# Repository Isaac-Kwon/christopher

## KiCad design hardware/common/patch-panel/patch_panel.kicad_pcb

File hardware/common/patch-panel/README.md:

# Menu patch panel board (common part)

Generated KiCad 10 schematic and **placement-only** PCB of the small board behind the operator panel that carries what the menu
plugging needs besides the letter jacks. Design basis: `hardware/common/design-brief.md` 4.3 (patch panel), 4.5 (test register, test voltage),
`hardware/common/diagonal-board.md` section 4 (what is *not* on the diagonal boards), `hardware/common/test-register/README.md` (J1 cable, J5 TEST lead),
`docs/decisions/0003-interfaces.md` 5.1, 5.2, 7. Build product of the scripts, do not edit by hand.

## Decision: letter jacks stay on the diagonal boards

The design brief puts the letter jacks on the diagonal-board backplane (4.4: "glyph jacks on a backplane PCB with fixed wiring"), and
`diagonal-board.md` section 4 says commons, register-cable jack and searching jack are *not* part of the diagonal nets and go on a separate small
board. So the patch panel is **not folded** into the diagonal boards; it is this separate board (339.5 x 160 mm, one board).

## Content

| Part | Count | Function |
|---|---:|---|
| `CM11..CM44` commons | 4 groups x 4 male D-sub 37 | the four jacks of a group are in parallel (26 lines): one letter can feed more than two scramblers |
| `JR1` / `JR2` register jack | 2 male D-sub 37 | `JR1` front (operator), `JR2` rear (cable to the test register J1), parallel; a cable between the test letter's jack and `JR1` brings that letter's 26 wires to the register |
| `JS1` searching jack + `TS1` hole field | 1 jack + 26 holes (2 x 13 pin socket) | a cable from the test letter's second jack to `JS1`; line k appears at hole k (silk A..Z) |
| `J_TEST` | 2-pole 5.08 terminal | 1 = `TEST` (register J5, +24 V during STROBE), 2 = 0 V |
| `PL1` test plug | flying lead (in the schematic, `on_board = no`) | the end of the TEST lead, pushed into ONE hole of `TS1` = the wire that gets the test voltage (the menu's input wire) |
| `J0V` | 2-pole 5.08 terminal (both pins one net) | the 0 V reference: ONE connection to the 0 V of the power supply (and to `J0V` on diagonal board D1) |
| `R1`, `C1`, 6 plated M3 holes | | `CHASSIS` (shells, holes) to 0 V by 1 Mohm || 10 nF (decision 0003 7.1) |

All jacks are **male** (decision 0003 5.1: boards and panel pins, cables female at both ends, 1:1), pins 1-26 = wire A..Z, **pins 27-29 tied to 0 V here**
(common side; the scrambler-side boards never tie them), 30-37 not connected, shell pads = `CHASSIS`. Layout: 85 x 30 mm grid, rows 1-4 = commons 1-4,
row 5 = `JR1`, `JR2`, `JS1` and the fourth slot with `TS1` (horizontal, hole letters on the silk), `J_TEST`, `J0V`. 4 layers (26-line commons).

## Files

| File | Purpose |
|---|---|
| `ki_common.py` | shared library (identical copy in the other two folders) |
| `gen_patch.py` | -> `patch_panel.kicad_pro/.kicad_sch` |
| `gen_patch_pcb.py` | placement -> `patch_panel.kicad_pcb` |
| `verify_patch.py` | ERC + netlist connectivity + test-plug simulation + negative tests |
| `verify_patch_pcb.py` | board vs schematic, DRC, geometry (pcbnew), negative test |

    python gen_patch.py && python gen_patch_pcb.py && python verify_patch.py && python verify_patch_pcb.py

Build output in `%LOCALAPPDATA%/christopher/patch-panel`.

## Results (KiCad 10.0.4)

| Item | Result |
|---|---|
| ERC (all severities) | 0 violations |
| Parts | 30 (19 jacks, `TS1`, `J_TEST`, `J0V`, `R1`, `C1`, 6 holes) + the flying plug `PL1` |
| Connectivity | each common wire = exactly the 4 jack pins of its group; `JR1`/`JR2` pin k on one net; `JS1` pin k = hole k only; 0 V net = pins 27-29 of all 19 jacks + `J_TEST` 2 + `J0V` + RC, no signal on it; CHASSIS separate from 0 V |
| Test-plug simulation | plug out: `TEST` isolated; plug in hole k (k = 1..26): `TEST` reaches exactly `JS1` pin k and hole k, nothing else |
| Negative tests | swapped wires on a common jack / on `JS1` / in the hole field, `TEST` <-> 0 V swapped on `J_TEST`, wire <-> 0 V pin on `JR2`: all detected |
| Placement DRC | **0 violations**; unconnected = ratsnest 470 (pcbnew count = sum(pads-1)); pad nets = schematic; grid and hole-field order checked from the board; negative test detected |

## Open questions

1. Who connects the register: the permanent register cable (J1) could also go straight to a letter jack; `JR1`/`JR2` are provided because the brief lists a register-cable jack on the panel.
   If the permanent cable is preferred, `JR2`/`JR1` can be dropped.
2. The test plug is a one-pin flying lead into a 2.54 pin-socket field. A sturdier banana/4 mm field and a plug with shrouded 24 V contact (touch protection, 24 V is extra-low voltage)
   are a panel-design choice; contact wear counts like the letter jacks.
3. Whether TEST should also be offered on a third letter (the British machine had a test plug per bank) is outside this design.
4. Board position and size (339.5 x 160) follow the commons grid (layout.md 3.10 "4 x 4 below the drive"); the real cut-out drawing is a mechanical task.
5. Routing is not done (user rule): 16 x 26 common nets (4 pads each), 26 register nets, 26 search nets.

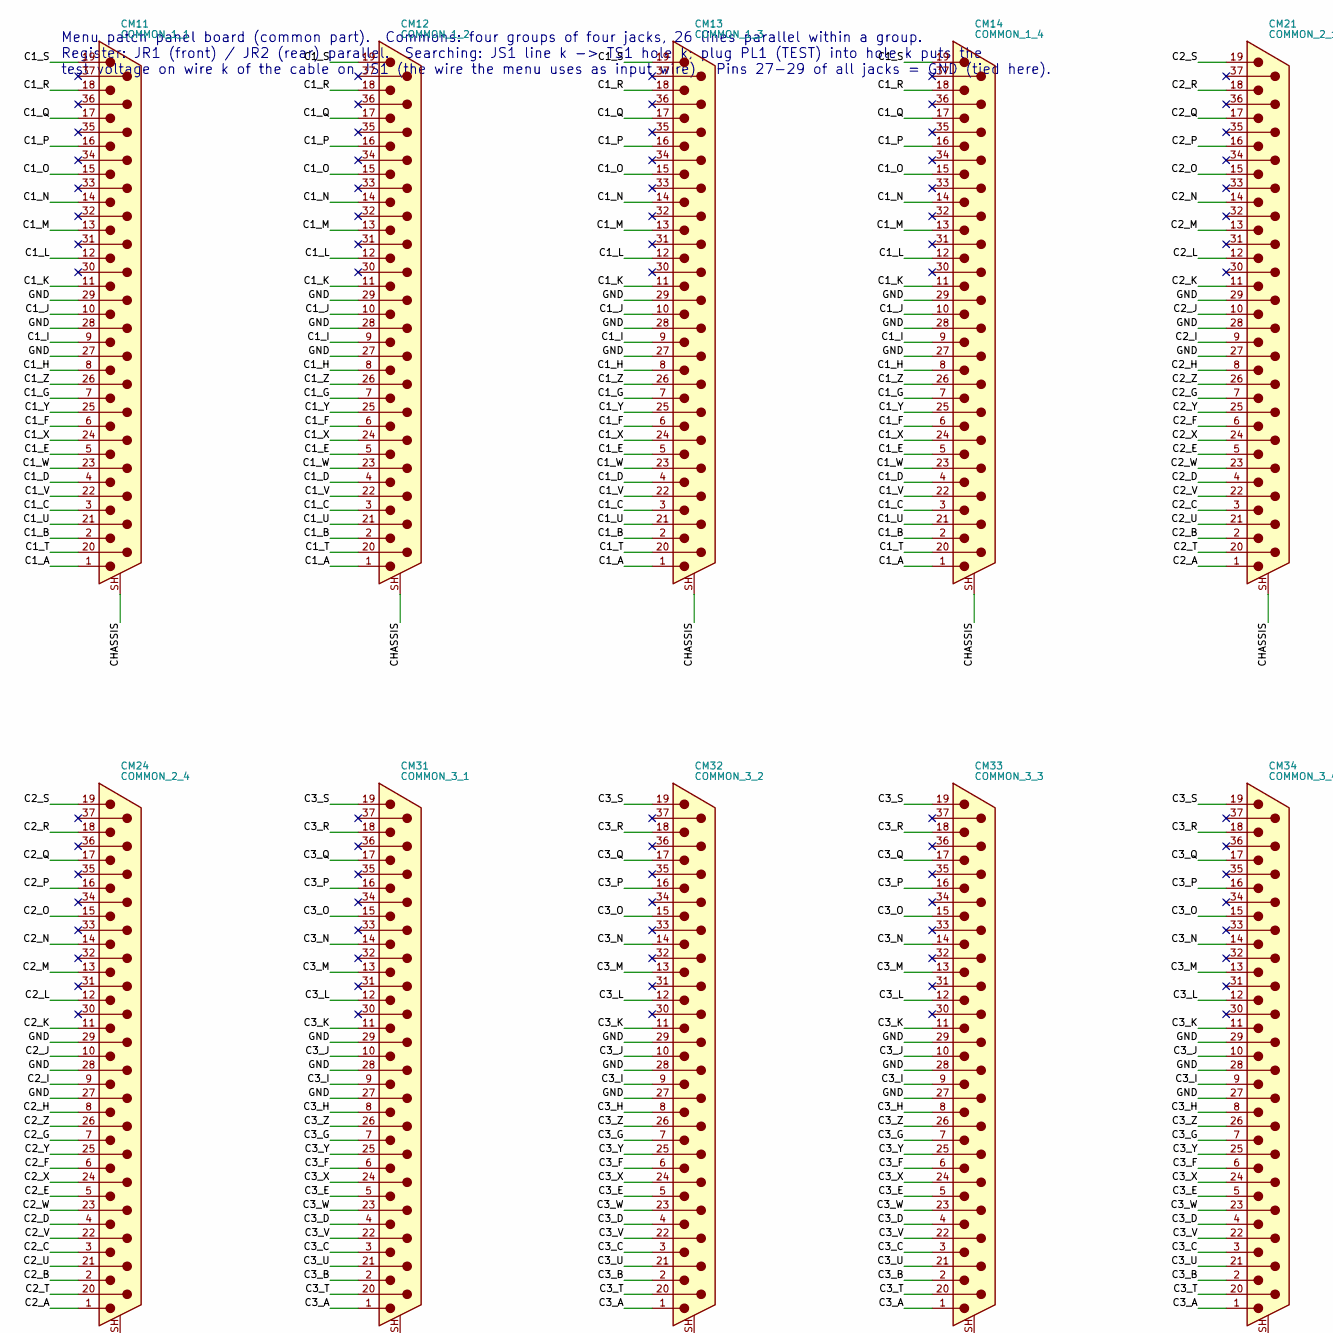
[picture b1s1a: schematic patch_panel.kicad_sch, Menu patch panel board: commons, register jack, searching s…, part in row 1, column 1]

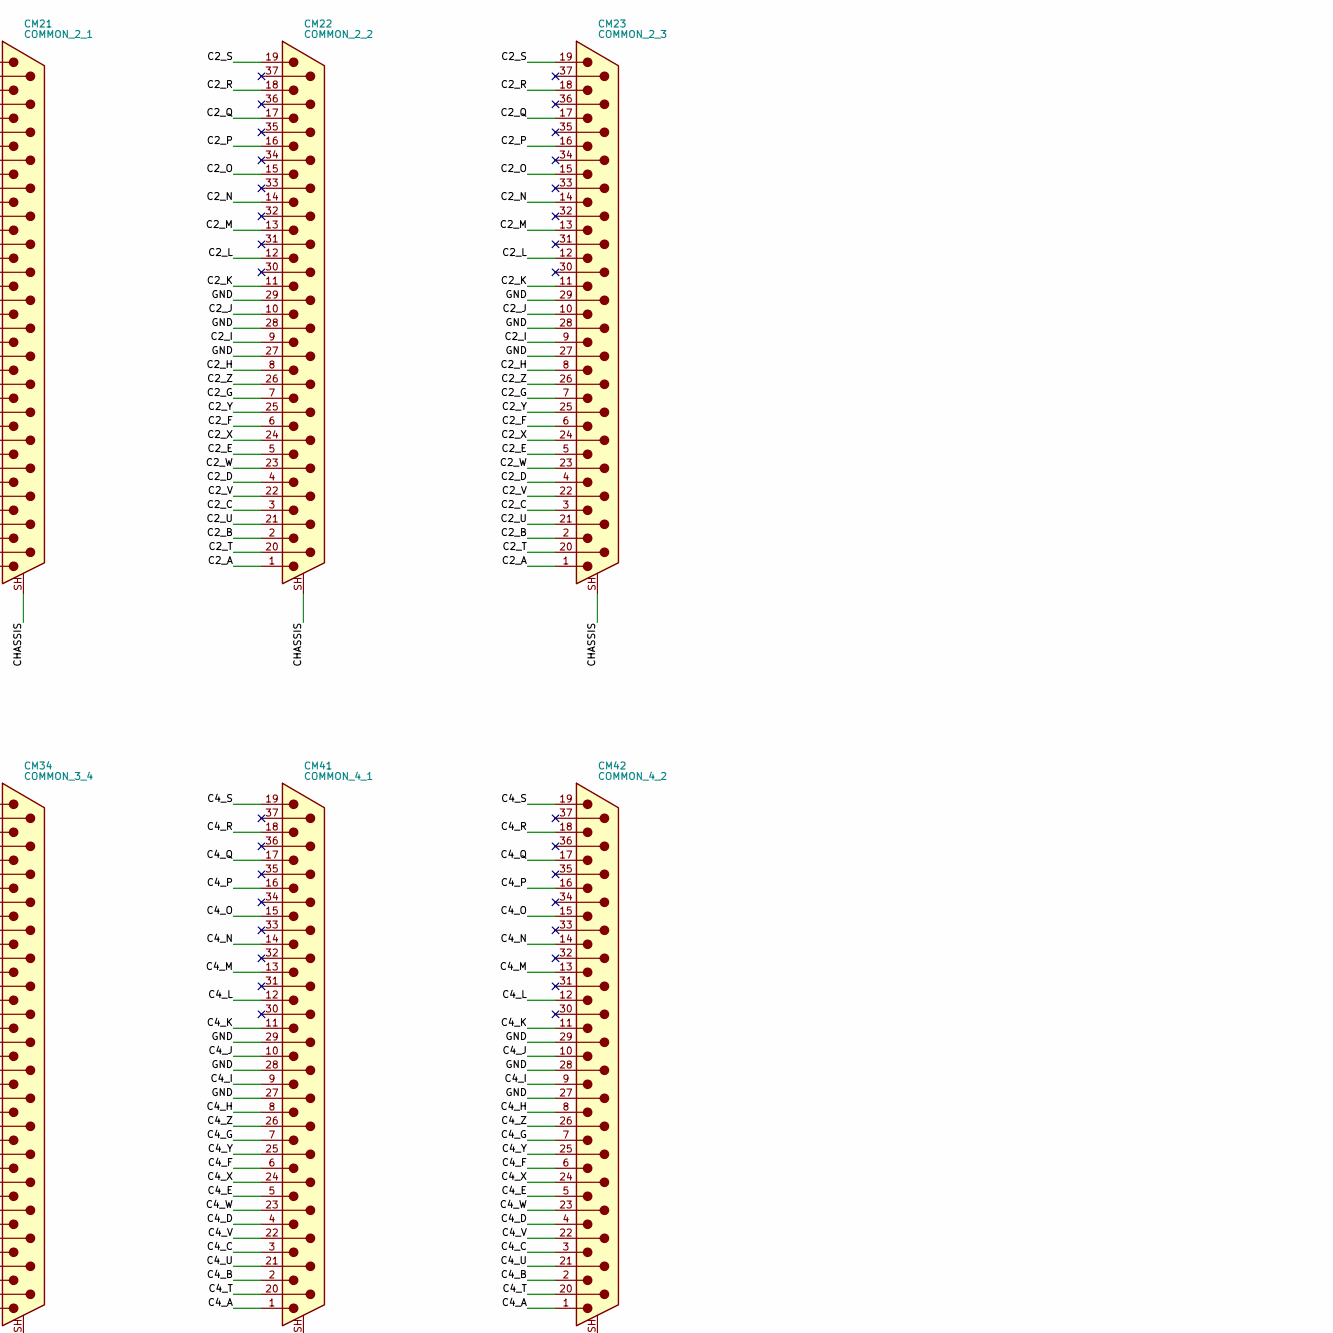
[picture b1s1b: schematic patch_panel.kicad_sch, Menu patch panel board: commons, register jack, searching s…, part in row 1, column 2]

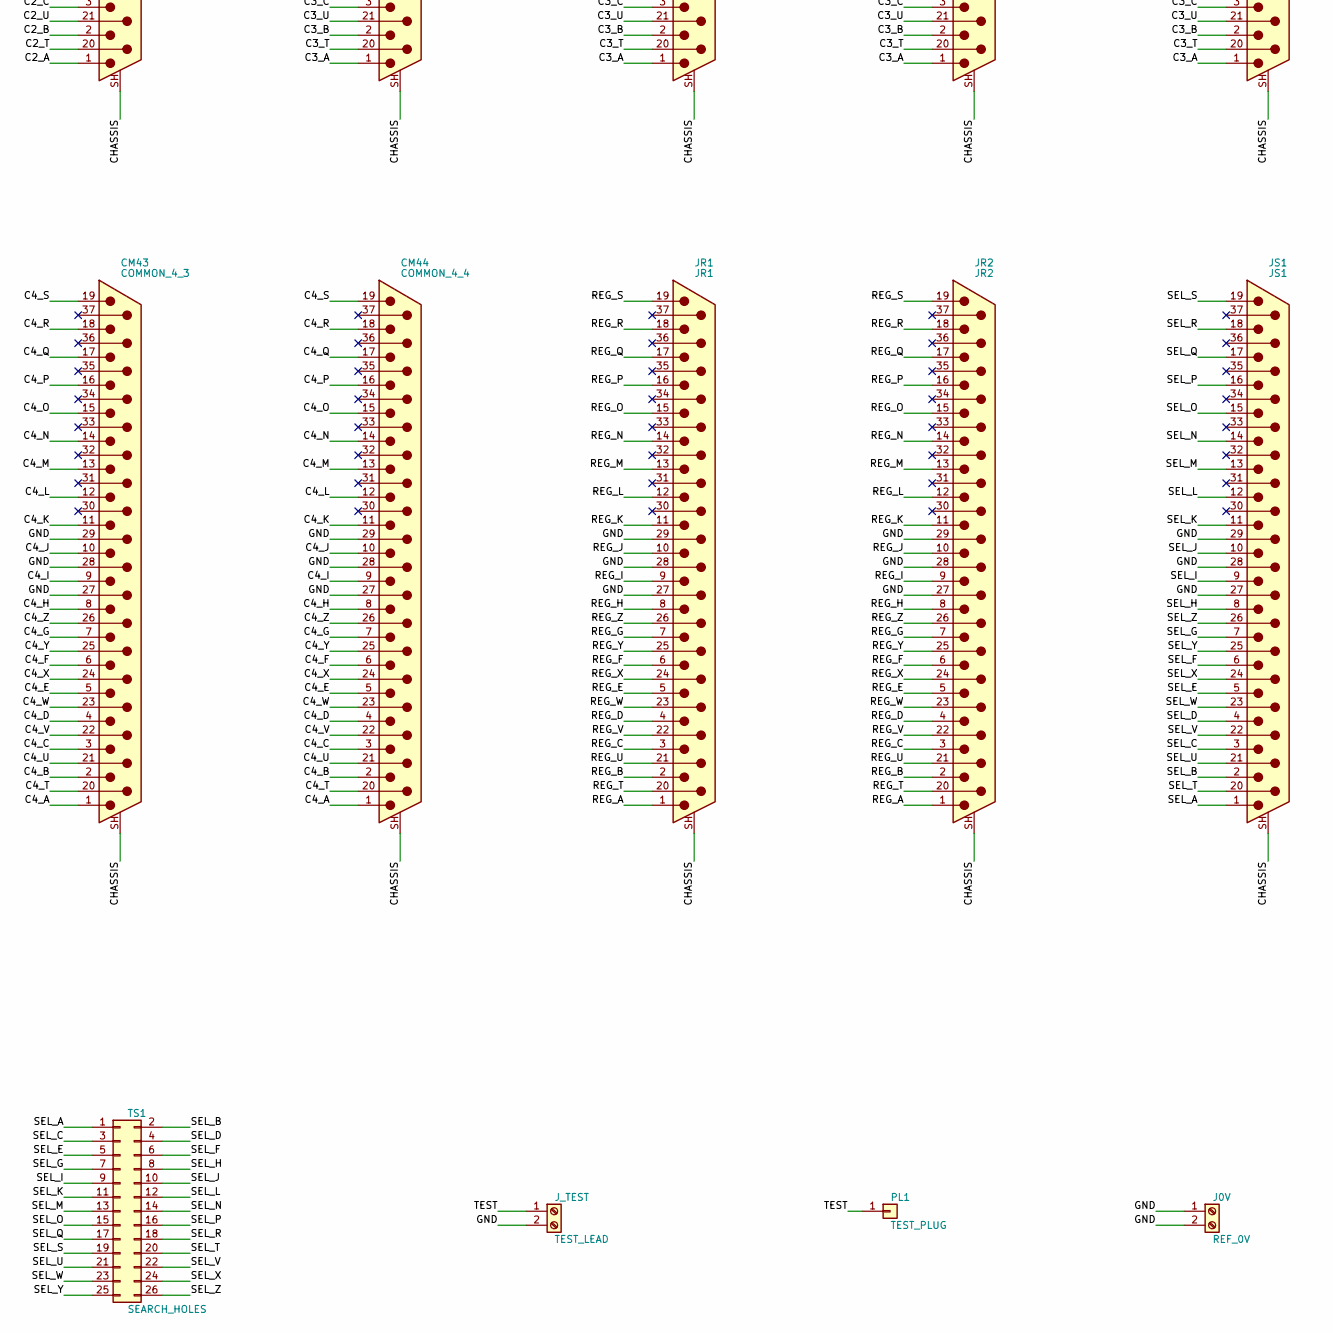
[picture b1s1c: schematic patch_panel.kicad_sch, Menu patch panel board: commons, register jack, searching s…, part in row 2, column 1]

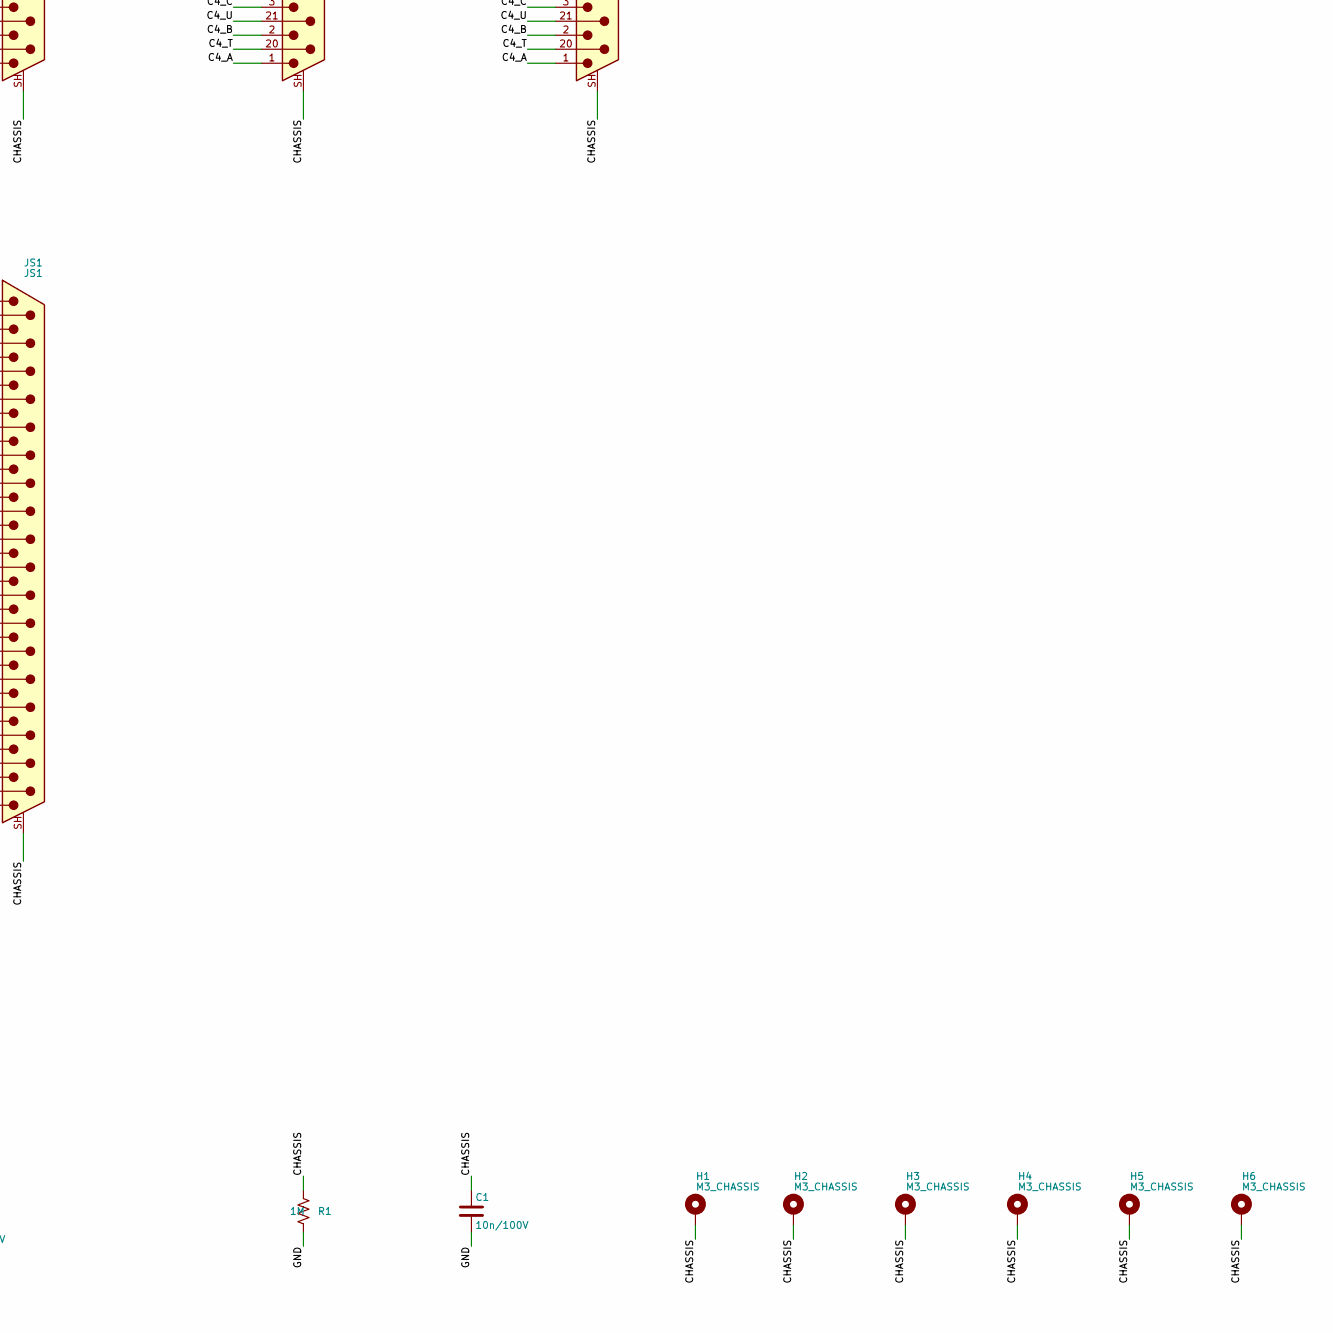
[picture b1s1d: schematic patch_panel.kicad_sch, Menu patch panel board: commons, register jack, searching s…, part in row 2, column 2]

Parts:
C1: 10n/100V; C_0805_2012Metric
CM11: COMMON_1_1; DSUB-37_Pins_Vertical_P2.77x2.84mm_MountingHoles
CM12: COMMON_1_2; DSUB-37_Pins_Vertical_P2.77x2.84mm_MountingHoles
CM13: COMMON_1_3; DSUB-37_Pins_Vertical_P2.77x2.84mm_MountingHoles
CM14: COMMON_1_4; DSUB-37_Pins_Vertical_P2.77x2.84mm_MountingHoles
CM21: COMMON_2_1; DSUB-37_Pins_Vertical_P2.77x2.84mm_MountingHoles
CM22: COMMON_2_2; DSUB-37_Pins_Vertical_P2.77x2.84mm_MountingHoles
CM23: COMMON_2_3; DSUB-37_Pins_Vertical_P2.77x2.84mm_MountingHoles
CM24: COMMON_2_4; DSUB-37_Pins_Vertical_P2.77x2.84mm_MountingHoles
CM31: COMMON_3_1; DSUB-37_Pins_Vertical_P2.77x2.84mm_MountingHoles
CM32: COMMON_3_2; DSUB-37_Pins_Vertical_P2.77x2.84mm_MountingHoles
CM33: COMMON_3_3; DSUB-37_Pins_Vertical_P2.77x2.84mm_MountingHoles
CM34: COMMON_3_4; DSUB-37_Pins_Vertical_P2.77x2.84mm_MountingHoles
CM41: COMMON_4_1; DSUB-37_Pins_Vertical_P2.77x2.84mm_MountingHoles
CM42: COMMON_4_2; DSUB-37_Pins_Vertical_P2.77x2.84mm_MountingHoles
CM43: COMMON_4_3; DSUB-37_Pins_Vertical_P2.77x2.84mm_MountingHoles
CM44: COMMON_4_4; DSUB-37_Pins_Vertical_P2.77x2.84mm_MountingHoles
H1, H2, H3, H4, H5, H6: M3_CHASSIS; MountingHole_3.2mm_M3_Pad
J0V: REF_0V; TerminalBlock_Phoenix_MKDS-1,5-2-5.08_1x02_P5.08mm_Horizont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
JR1: JR1; DSUB-37_Pins_Vertical_P2.77x2.84mm_MountingHoles
JR2: JR2; DSUB-37_Pins_Vertical_P2.77x2.84mm_MountingHoles
JS1: JS1; DSUB-37_Pins_Vertical_P2.77x2.84mm_MountingHoles
J_TEST: TEST_LEAD; TerminalBlock_Phoenix_MKDS-1,5-2-5.08_1x02_P5.08mm_Horizont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
PL1: TEST_PLUG
R1: 1M; R_0603_1608Metric
TS1: SEARCH_HOLES; PinSocket_2x13_P2.54mm_Vertical

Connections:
/C1_A: CM11.1, CM12.1, CM13.1, CM14.1
/C1_B: CM11.2, CM12.2, CM13.2, CM14.2
/C1_C: CM11.3, CM12.3, CM13.3, CM14.3
/C1_D: CM11.4, CM12.4, CM13.4, CM14.4
/C1_E: CM11.5, CM12.5, CM13.5, CM14.5
/C1_F: CM11.6, CM12.6, CM13.6, CM14.6
/C1_G: CM11.7, CM12.7, CM13.7, CM14.7
/C1_H: CM11.8, CM12.8, CM13.8, CM14.8
/C1_I: CM11.9, CM12.9, CM13.9, CM14.9
/C1_J: CM11.10, CM12.10, CM13.10, CM14.10
/C1_K: CM11.11, CM12.11, CM13.11, CM14.11
/C1_L: CM11.12, CM12.12, CM13.12, CM14.12
/C1_M: CM11.13, CM12.13, CM13.13, CM14.13
/C1_N: CM11.14, CM12.14, CM13.14, CM14.14
/C1_O: CM11.15, CM12.15, CM13.15, CM14.15
/C1_P: CM11.16, CM12.16, CM13.16, CM14.16
/C1_Q: CM11.17, CM12.17, CM13.17, CM14.17
/C1_R: CM11.18, CM12.18, CM13.18, CM14.18
/C1_S: CM11.19, CM12.19, CM13.19, CM14.19
/C1_T: CM11.20, CM12.20, CM13.20, CM14.20
/C1_U: CM11.21, CM12.21, CM13.21, CM14.21
/C1_V: CM11.22, CM12.22, CM13.22, CM14.22
/C1_W: CM11.23, CM12.23, CM13.23, CM14.23
/C1_X: CM11.24, CM12.24, CM13.24, CM14.24
/C1_Y: CM11.25, CM12.25, CM13.25, CM14.25
/C1_Z: CM11.26, CM12.26, CM13.26, CM14.26
/C2_A: CM21.1, CM22.1, CM23.1, CM24.1
/C2_B: CM21.2, CM22.2, CM23.2, CM24.2
/C2_C: CM21.3, CM22.3, CM23.3, CM24.3
/C2_D: CM21.4, CM22.4, CM23.4, CM24.4
/C2_E: CM21.5, CM22.5, CM23.5, CM24.5
/C2_F: CM21.6, CM22.6, CM23.6, CM24.6
/C2_G: CM21.7, CM22.7, CM23.7, CM24.7
/C2_H: CM21.8, CM22.8, CM23.8, CM24.8
/C2_I: CM21.9, CM22.9, CM23.9, CM24.9
/C2_J: CM21.10, CM22.10, CM23.10, CM24.10
/C2_K: CM21.11, CM22.11, CM23.11, CM24.11
/C2_L: CM21.12, CM22.12, CM23.12, CM24.12
/C2_M: CM21.13, CM22.13, CM23.13, CM24.13
/C2_N: CM21.14, CM22.14, CM23.14, CM24.14
/C2_O: CM21.15, CM22.15, CM23.15, CM24.15
/C2_P: CM21.16, CM22.16, CM23.16, CM24.16
/C2_Q: CM21.17, CM22.17, CM23.17, CM24.17
/C2_R: CM21.18, CM22.18, CM23.18, CM24.18
/C2_S: CM21.19, CM22.19, CM23.19, CM24.19
/C2_T: CM21.20, CM22.20, CM23.20, CM24.20
/C2_U: CM21.21, CM22.21, CM23.21, CM24.21
/C2_V: CM21.22, CM22.22, CM23.22, CM24.22
/C2_W: CM21.23, CM22.23, CM23.23, CM24.23
/C2_X: CM21.24, CM22.24, CM23.24, CM24.24
/C2_Y: CM21.25, CM22.25, CM23.25, CM24.25
/C2_Z: CM21.26, CM22.26, CM23.26, CM24.26
/C3_A: CM31.1, CM32.1, CM33.1, CM34.1
/C3_B: CM31.2, CM32.2, CM33.2, CM34.2
/C3_C: CM31.3, CM32.3, CM33.3, CM34.3
/C3_D: CM31.4, CM32.4, CM33.4, CM34.4
/C3_E: CM31.5, CM32.5, CM33.5, CM34.5
/C3_F: CM31.6, CM32.6, CM33.6, CM34.6
/C3_G: CM31.7, CM32.7, CM33.7, CM34.7
/C3_H: CM31.8, CM32.8, CM33.8, CM34.8
/C3_I: CM31.9, CM32.9, CM33.9, CM34.9
/C3_J: CM31.10, CM32.10, CM33.10, CM34.10
/C3_K: CM31.11, CM32.11, CM33.11, CM34.11
/C3_L: CM31.12, CM32.12, CM33.12, CM34.12
/C3_M: CM31.13, CM32.13, CM33.13, CM34.13
/C3_N: CM31.14, CM32.14, CM33.14, CM34.14
/C3_O: CM31.15, CM32.15, CM33.15, CM34.15
/C3_P: CM31.16, CM32.16, CM33.16, CM34.16
/C3_Q: CM31.17, CM32.17, CM33.17, CM34.17
/C3_R: CM31.18, CM32.18, CM33.18, CM34.18
/C3_S: CM31.19, CM32.19, CM33.19, CM34.19
/C3_T: CM31.20, CM32.20, CM33.20, CM34.20
/C3_U: CM31.21, CM32.21, CM33.21, CM34.21
/C3_V: CM31.22, CM32.22, CM33.22, CM34.22
/C3_W: CM31.23, CM32.23, CM33.23, CM34.23
/C3_X: CM31.24, CM32.24, CM33.24, CM34.24
/C3_Y: CM31.25, CM32.25, CM33.25, CM34.25
/C3_Z: CM31.26, CM32.26, CM33.26, CM34.26
/C4_A: CM41.1, CM42.1, CM43.1, CM44.1
/C4_B: CM41.2, CM42.2, CM43.2, CM44.2
/C4_C: CM41.3, CM42.3, CM43.3, CM44.3
/C4_D: CM41.4, CM42.4, CM43.4, CM44.4
/C4_E: CM41.5, CM42.5, CM43.5, CM44.5
/C4_F: CM41.6, CM42.6, CM43.6, CM44.6
/C4_G: CM41.7, CM42.7, CM43.7, CM44.7
/C4_H: CM41.8, CM42.8, CM43.8, CM44.8
/C4_I: CM41.9, CM42.9, CM43.9, CM44.9
/C4_J: CM41.10, CM42.10, CM43.10, CM44.10
/C4_K: CM41.11, CM42.11, CM43.11, CM44.11
/C4_L: CM41.12, CM42.12, CM43.12, CM44.12
/C4_M: CM41.13, CM42.13, CM43.13, CM44.13
/C4_N: CM41.14, CM42.14, CM43.14, CM44.14
/C4_O: CM41.15, CM42.15, CM43.15, CM44.15
/C4_P: CM41.16, CM42.16, CM43.16, CM44.16
/C4_Q: CM41.17, CM42.17, CM43.17, CM44.17
/C4_R: CM41.18, CM42.18, CM43.18, CM44.18
/C4_S: CM41.19, CM42.19, CM43.19, CM44.19
/C4_T: CM41.20, CM42.20, CM43.20, CM44.20
/C4_U: CM41.21, CM42.21, CM43.21, CM44.21
/C4_V: CM41.22, CM42.22, CM43.22, CM44.22
/C4_W: CM41.23, CM42.23, CM43.23, CM44.23
/C4_X: CM41.24, CM42.24, CM43.24, CM44.24
/C4_Y: CM41.25, CM42.25, CM43.25, CM44.25
/C4_Z: CM41.26, CM42.26, CM43.26, CM44.26
/CHASSIS: C1.1, CM11.SH (PAD), CM12.SH (PAD), CM13.SH (PAD), CM14.SH (PAD), CM21.SH (PAD), CM22.SH (PAD), CM23.SH (PAD), CM24.SH (PAD), CM31.SH (PAD), CM32.SH (PAD), CM33.SH (PAD), CM34.SH (PAD), CM41.SH (PAD), CM42.SH (PAD), CM43.SH (PAD), CM44.SH (PAD), H1.1, H2.1, H3.1, H4.1, H5.1, H6.1, JR1.SH (PAD), JR2.SH (PAD), JS1.SH (PAD), R1.1
/GND: C1.2, CM11.27, CM11.28, CM11.29, CM12.27, CM12.28, CM12.29, CM13.27, CM13.28, CM13.29, CM14.27, CM14.28, CM14.29, CM21.27, CM21.28, CM21.29, CM22.27, CM22.28, CM22.29, CM23.27, CM23.28, CM23.29, CM24.27, CM24.28, CM24.29, CM31.27, CM31.28, CM31.29, CM32.27, CM32.28, CM32.29, CM33.27, CM33.28, CM33.29, CM34.27, CM34.28, CM34.29, CM41.27, CM41.28, CM41.29, CM42.27, CM42.28, CM42.29, CM43.27, CM43.28, CM43.29, CM44.27, CM44.28, CM44.29, J0V.1, J0V.2, JR1.27, JR1.28, JR1.29, JR2.27, JR2.28, JR2.29, JS1.27, JS1.28, JS1.29, J_TEST.2, R1.2
/REG_A: JR1.1, JR2.1
/REG_B: JR1.2, JR2.2
/REG_C: JR1.3, JR2.3
/REG_D: JR1.4, JR2.4
/REG_E: JR1.5, JR2.5
/REG_F: JR1.6, JR2.6
/REG_G: JR1.7, JR2.7
/REG_H: JR1.8, JR2.8
/REG_I: JR1.9, JR2.9
/REG_J: JR1.10, JR2.10
/REG_K: JR1.11, JR2.11
/REG_L: JR1.12, JR2.12
/REG_M: JR1.13, JR2.13
/REG_N: JR1.14, JR2.14
/REG_O: JR1.15, JR2.15
/REG_P: JR1.16, JR2.16
/REG_Q: JR1.17, JR2.17
/REG_R: JR1.18, JR2.18
/REG_S: JR1.19, JR2.19
/REG_T: JR1.20, JR2.20
/REG_U: JR1.21, JR2.21
/REG_V: JR1.22, JR2.22
/REG_W: JR1.23, JR2.23
/REG_X: JR1.24, JR2.24
/REG_Y: JR1.25, JR2.25
/REG_Z: JR1.26, JR2.26
/SEL_A: JS1.1, TS1.1
/SEL_B: JS1.2, TS1.2
/SEL_C: JS1.3, TS1.3
/SEL_D: JS1.4, TS1.4
/SEL_E: JS1.5, TS1.5
/SEL_F: JS1.6, TS1.6
/SEL_G: JS1.7, TS1.7
/SEL_H: JS1.8, TS1.8
/SEL_I: JS1.9, TS1.9
/SEL_J: JS1.10, TS1.10
/SEL_K: JS1.11, TS1.11
/SEL_L: JS1.12, TS1.12
/SEL_M: JS1.13, TS1.13
/SEL_N: JS1.14, TS1.14
/SEL_O: JS1.15, TS1.15
/SEL_P: JS1.16, TS1.16
/SEL_Q: JS1.17, TS1.17
/SEL_R: JS1.18, TS1.18
/SEL_S: JS1.19, TS1.19
/SEL_T: JS1.20, TS1.20
/SEL_U: JS1.21, TS1.21
/SEL_V: JS1.22, TS1.22
/SEL_W: JS1.23, TS1.23
/SEL_X: JS1.24, TS1.24
/SEL_Y: JS1.25, TS1.25
/SEL_Z: JS1.26, TS1.26
/TEST: J_TEST.1, PL1.1

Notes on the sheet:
Menu patch panel board (common part). Commons: four groups of four jacks, 26 lines parallel within a group. Register: JR1 (front) / JR2 (rear) parallel. Searching: JS1 line k -> TS1 hole k; plug PL1 (TEST) into hole k puts the test voltage on wire k of the cable on JS1 (the wire the menu uses as in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

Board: 4 copper layers, 30 parts (0 on the bottom side), 158 nets, no tracks yet.
